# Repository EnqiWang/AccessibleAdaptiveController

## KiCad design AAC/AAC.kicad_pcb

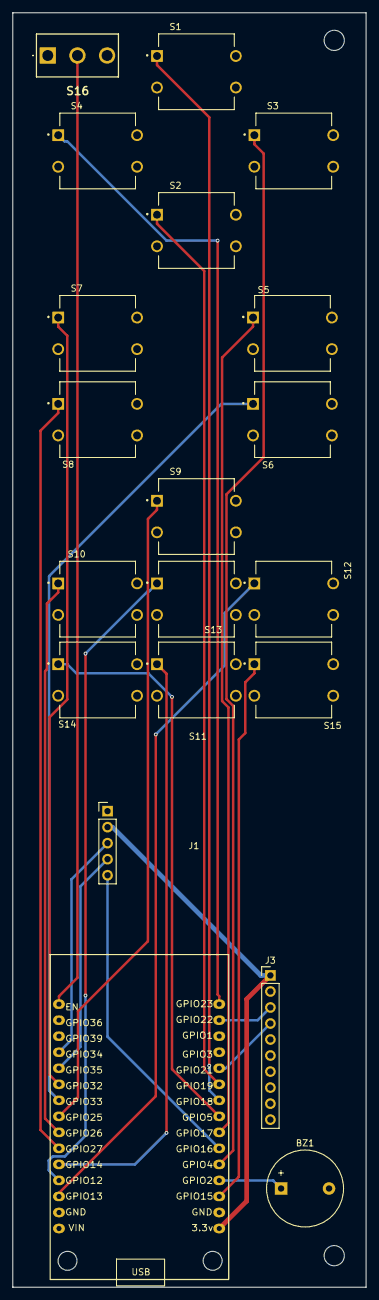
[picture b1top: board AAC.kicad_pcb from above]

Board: 2 copper layers, 56.0 x 202.0 mm, 21 parts (0 on the bottom side), 24 nets.

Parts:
BZ1: Buzzer; Buzzer_12x9.5RM7.6
J1: Conn_01x05; KY-023
J3: Conn_01x10; BNO_080
MF1: MountingHole_3.2mm_M3
S1, S2, S3, S4, S5, S6, S7, S8, S9, S10, S11, S12, S13, S14, S15: B3F-4055; SW_B3F-4055
S16: SS-12D10G5; SS12D10G5
U1: ESP32 Module; ESP32_30pin

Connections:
+3V3: J1.2, J3.1, U1.16 (3.3v)
/BTN_A: S12.1, U1.3 (GPIO13)
/BTN_B: S11.1, U1.5 (GPIO14)
/BTN_BACK: S14.1, U1.23 (GPIO5)
/BTN_DOWN: S2.1, U1.25 (GPIO19)
/BTN_HOME: S13.1, U1.4 (GPIO12)
/BTN_L: S8.1, U1.6 (GPIO27)
/BTN_LEFT: S4.1, U1.30 (GPIO23)
/BTN_R: S6.1, U1.9 (GPIO33)
/BTN_RIGHT: S3.1, U1.20 (GPIO4)
/BTN_START: S15.1, U1.18 (GPIO15)
/BTN_UP: S1.1, U1.24 (GPIO18)
/BTN_X: S9.1, U1.8 (GPIO25)
/BTN_Y: S10.1, U1.7 (GPIO26)
/BTN_ZL: S7.1, U1.10 (GPIO32)
/BTN_ZR: S5.1, U1.22 (GPIO17)
/BUZZER_GPIO: BZ1.1 (+), U1.19 (GPIO2)
/EN: S16.2 (COM), U1.15 (EN)
/JOY_SW: J1.5, U1.21 (GPIO16)
/JOY_X: J1.3, U1.12 (GPIO34)
/JOY_Y: J1.4, U1.11 (GPIO35)
/SCL: J3.3, U1.29 (GPIO22)
/SDA: J3.4, U1.26 (GPIO21)
GND: BZ1.2 (-), J1.1, J3.2, S1.4, S2.4, S3.4, S4.4, S5.4, S6.4, S7.4, S8.4, S9.4, S10.4, S11.4, S12.4, S13.4, S14.4, S15.4, S16.3 (NO), U1.2 (GND), U1.17 (GND)

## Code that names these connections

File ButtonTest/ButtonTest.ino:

#include <dummy.h>

// Button + joystick test for ESP32. Open Serial Monitor at 115200.
// Press every button once; the sketch tracks which are confirmed.
// Send 's' in the Serial Monitor to see the current checklist.

const int JOY_X = 34, JOY_Y = 35, JOY_SW = 16;
const int BUZZER_PIN = 2;

const int buttonPins[] = {13, 14, 25, 26, 27, 32, 33, 17, 18, 19, 23, 4, 36, 15, 5};
const char* buttonNames[] = {"A", "B", "X", "Y", "L", "ZL", "R", "ZR",
                             "UP", "DOWN", "LEFT", "RIGHT", "HOME", "START", "BACK"};
const int N = sizeof(buttonPins) / sizeof(buttonPins[0]);

bool raw[N], stable[N], tested[N];
unsigned long changed[N];
bool swRaw = false, swStable = false, swTested = false;
unsigned long swChanged = 0;
bool joyPrint = true;  

int xMin = 4095, xMax = 0, yMin = 4095, yMax = 0;
unsigned long lastJoyPrint = 0;

void printChecklist() {
  int done = swTested ? 1 : 0;
  for (int i = 0; i < N; i++) if (tested[i]) done++;
  Serial.printf("\n--- %d/%d tested ---\n", done, N + 1);
  Serial.print("Still untested: ");
  bool any = false;
  for (int i = 0; i < N; i++) if (!tested[i]) { Serial.print(buttonNames[i]); Serial.print(" "); any = true; }
  if (!swTested) { Serial.print("JOYSTICK_SW "); any = true; }
  if (!any) Serial.print("none, all buttons work!");
  Serial.println("\n");
}

void setup() {
  Serial.begin(115200);
  delay(800);
  Serial.println("\n=== BUTTON TEST ===");

  for (int i = 0; i < N; i++) {
    pinMode(buttonPins[i], buttonPins[i] >= 34 ? INPUT : INPUT_PULLUP);  // GPIO 34-39 have no internal pull-up
    raw[i] = stable[i] = (digitalRead(buttonPins[i]) == LOW);
    changed[i] = millis();
    tested[i] = false;
    if (stable[i]) Serial.printf("WARNING: %s (GPIO %d) reads pressed at boot. Short to GND or stuck?\n",
                                 buttonNames[i], buttonPins[i]);
  }
  pinMode(JOY_SW, INPUT_PULLUP);
  pinMode(BUZZER_PIN, OUTPUT);
  analogReadResolution(12);
  analogSetAttenuation(ADC_11db);

  printChecklist();
}

void loop() {
  unsigned long now = millis();

  for (int i = 0; i < N; i++) {
    bool p = (digitalRead(buttonPins[i]) == LOW);
    if (p != raw[i]) { raw[i] = p; changed[i] = now; }
    if (raw[i] != stable[i] && now - changed[i] >= 15) {
      stable[i] = raw[i];
      Serial.printf("%-6s (GPIO %2d) %s\n", buttonNames[i], buttonPins[i],
                    stable[i] ? "PRESSED" : "released");
      if (stable[i]) {
        digitalWrite(BUZZER_PIN, HIGH); delay(15); digitalWrite(BUZZER_PIN, LOW);
        if (!tested[i]) { tested[i] = true; printChecklist(); }
      }
    }
  }

  bool sp = (digitalRead(JOY_SW) == LOW);
  if (sp != swRaw) { swRaw = sp; swChanged = now; }
  if (swRaw != swStable && now - swChanged >= 15) {
    swStable = swRaw;
    Serial.println(swStable ? "JOYSTICK_SW PRESSED" : "JOYSTICK_SW released");
    if (swStable && !swTested) { swTested = true; printChecklist(); }
  }

  // Joystick: print every 300 ms
  int x = analogRead(JOY_X), y = analogRead(JOY_Y);
  xMin = min(xMin, x); xMax = max(xMax, x);
  yMin = min(yMin, y); yMax = max(yMax, y);
    if (joyPrint && now - lastJoyPrint >= 300) {
    lastJoyPrint = now;
    Serial.printf("Joystick X=%4d (min %4d max %4d)  Y=%4d (min %4d max %4d)\n",
                  x, xMin, xMax, y, yMin, yMax);
  }

  if (Serial.available()) {
    char c = Serial.read();
    if (c == 's') printChecklist();
    if (c == 'j') joyPrint = !joyPrint;
  }
}
